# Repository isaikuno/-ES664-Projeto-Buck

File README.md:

# -ES664-Projeto-Buck
PCB de um projeto Buck feito no KiCad em 2024.2

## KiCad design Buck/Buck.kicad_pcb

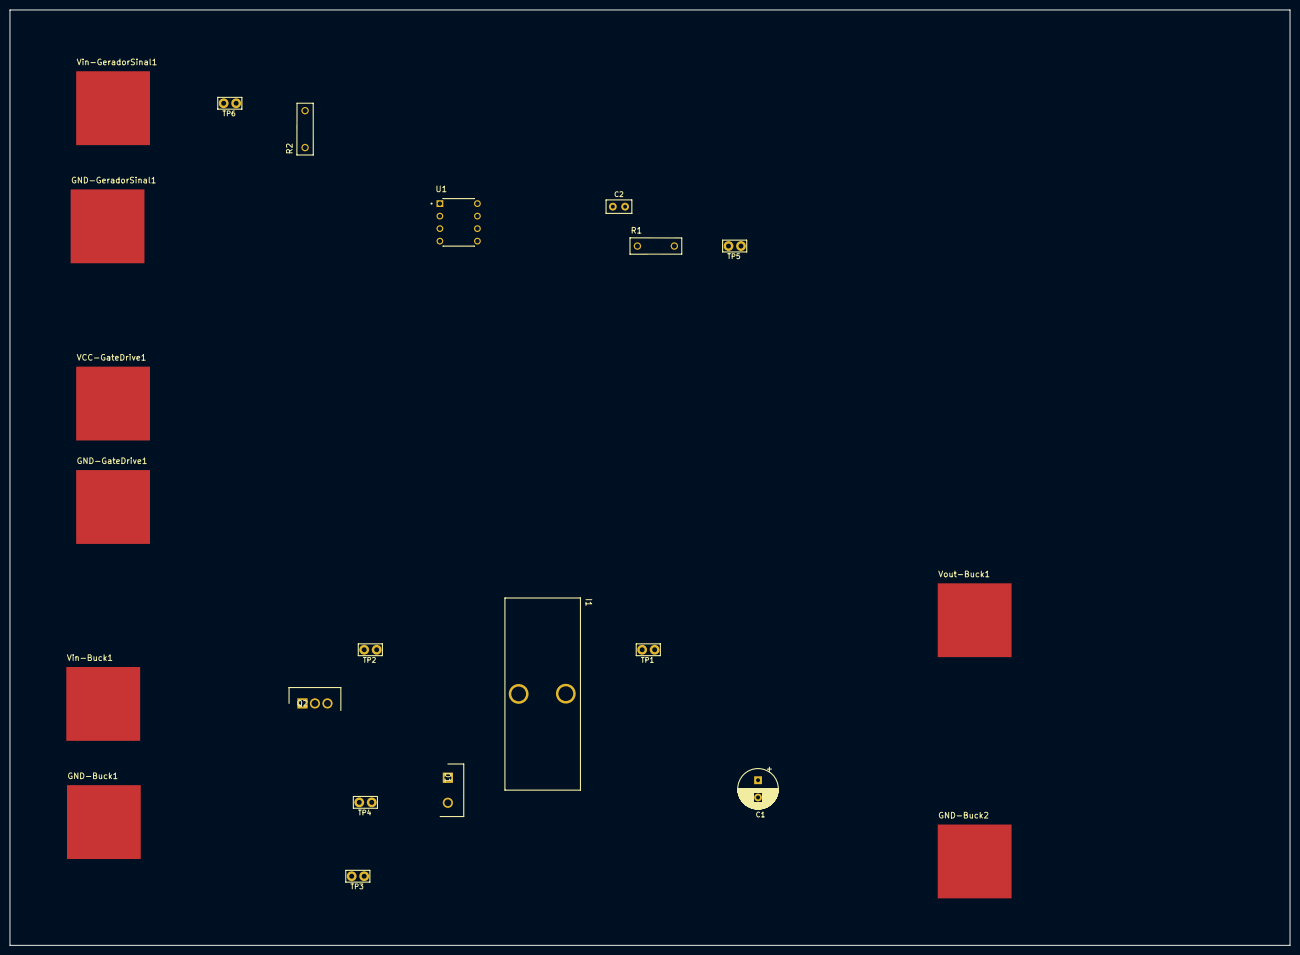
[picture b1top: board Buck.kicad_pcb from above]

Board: 2 copper layers, 260.0 x 190.0 mm, 22 parts (0 on the bottom side), 10 nets, no tracks yet.

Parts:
C1: 83.33uF; CP_Radial_D8.0mm_P3.50mm
C2: 0.1uF; C_Disc_D5.0mm_W2.5mm_P2.50mm
D1: RHRP30120; TO508P480X1016X2261-2P
GND-Buck1: SMD50
GND-Buck2: SMD50
GND-GateDrive1: SMD50
GND-GeradorSinal1: SMD50
I1: 30uH; INDUTOR-NUCLEO-FERRITE
Q2: IRFZ44; TO254P465X1024X2050-3P
R1: 15ohm; THDRESISTOR-1_4W
R2: 270 ohm; THDRESISTOR-1_4W
TP1, TP2, TP3, TP4, TP5, TP6: TestPoint_Alt; TestPoint_Bridge_Pitch2.54mm_Drill1.0mm
U1: HCPL-3180; DIP762W65P254L9650H470Q8
VCC-GateDrive1: SMD50
Vin-Buck1: SMD50
Vin-GeradorSinal1: SMD50
Vout-Buck1: SMD50

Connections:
15V: C2.1, U1.8 (VCC), VCC-GateDrive1.P$1
/DRIVE_SIGNAL: Q2.1 (G), R1.P22 (2), TP5.1
GND: C2.2, GND-GateDrive1.P$1, GND-GeradorSinal1.P$1, U1.3 (CATHODE), U1.5 (VEE)
unnamed: C1.2, D1.2 (A), GND-Buck1.P$1, GND-Buck2.P$1, TP3.1
unnamed: D1.1 (K), I1.A1, Q2.3 (S), TP2.1
unnamed: C1.1, I1.A2, TP1.1, Vout-Buck1.P$1
unnamed: Q2.2 (D), TP4.1, Vin-Buck1.P$1
unnamed: R1.P21 (1), U1.6 (VO), U1.7 (VO)
unnamed: R2.P21 (1), U1.2 (ANODE)
unnamed: R2.P22 (2), TP6.1, Vin-GeradorSinal1.P$1

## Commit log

2024-11-08 [IMPLEMENED] Schematic
2024-11-08 [SAVED]
